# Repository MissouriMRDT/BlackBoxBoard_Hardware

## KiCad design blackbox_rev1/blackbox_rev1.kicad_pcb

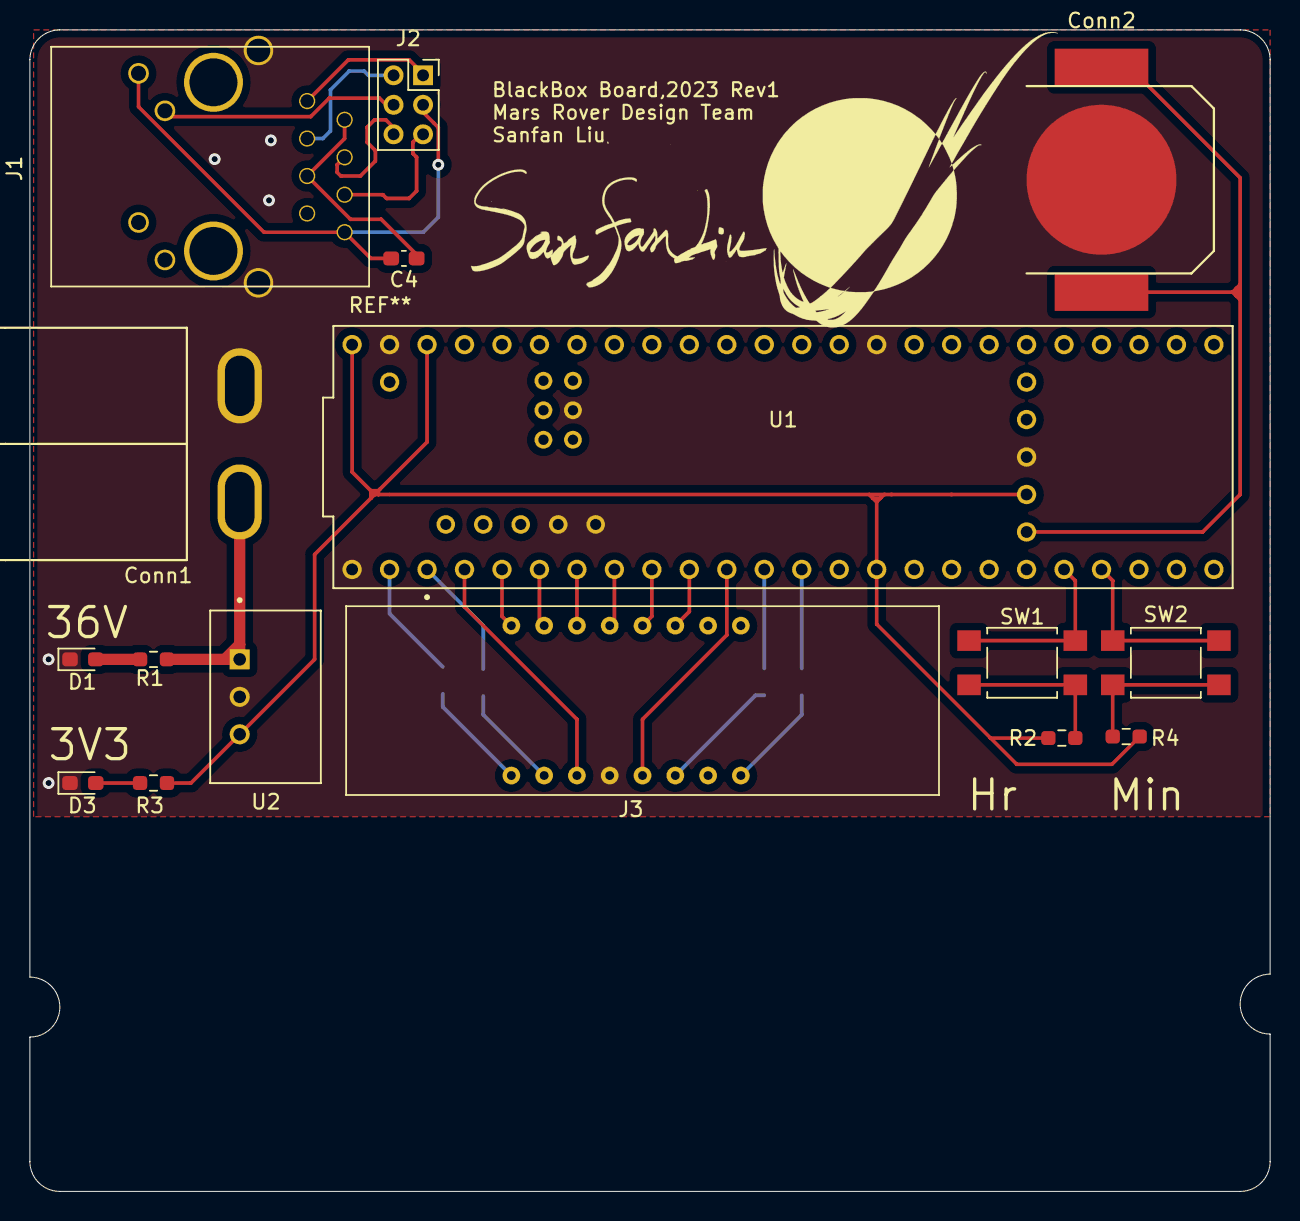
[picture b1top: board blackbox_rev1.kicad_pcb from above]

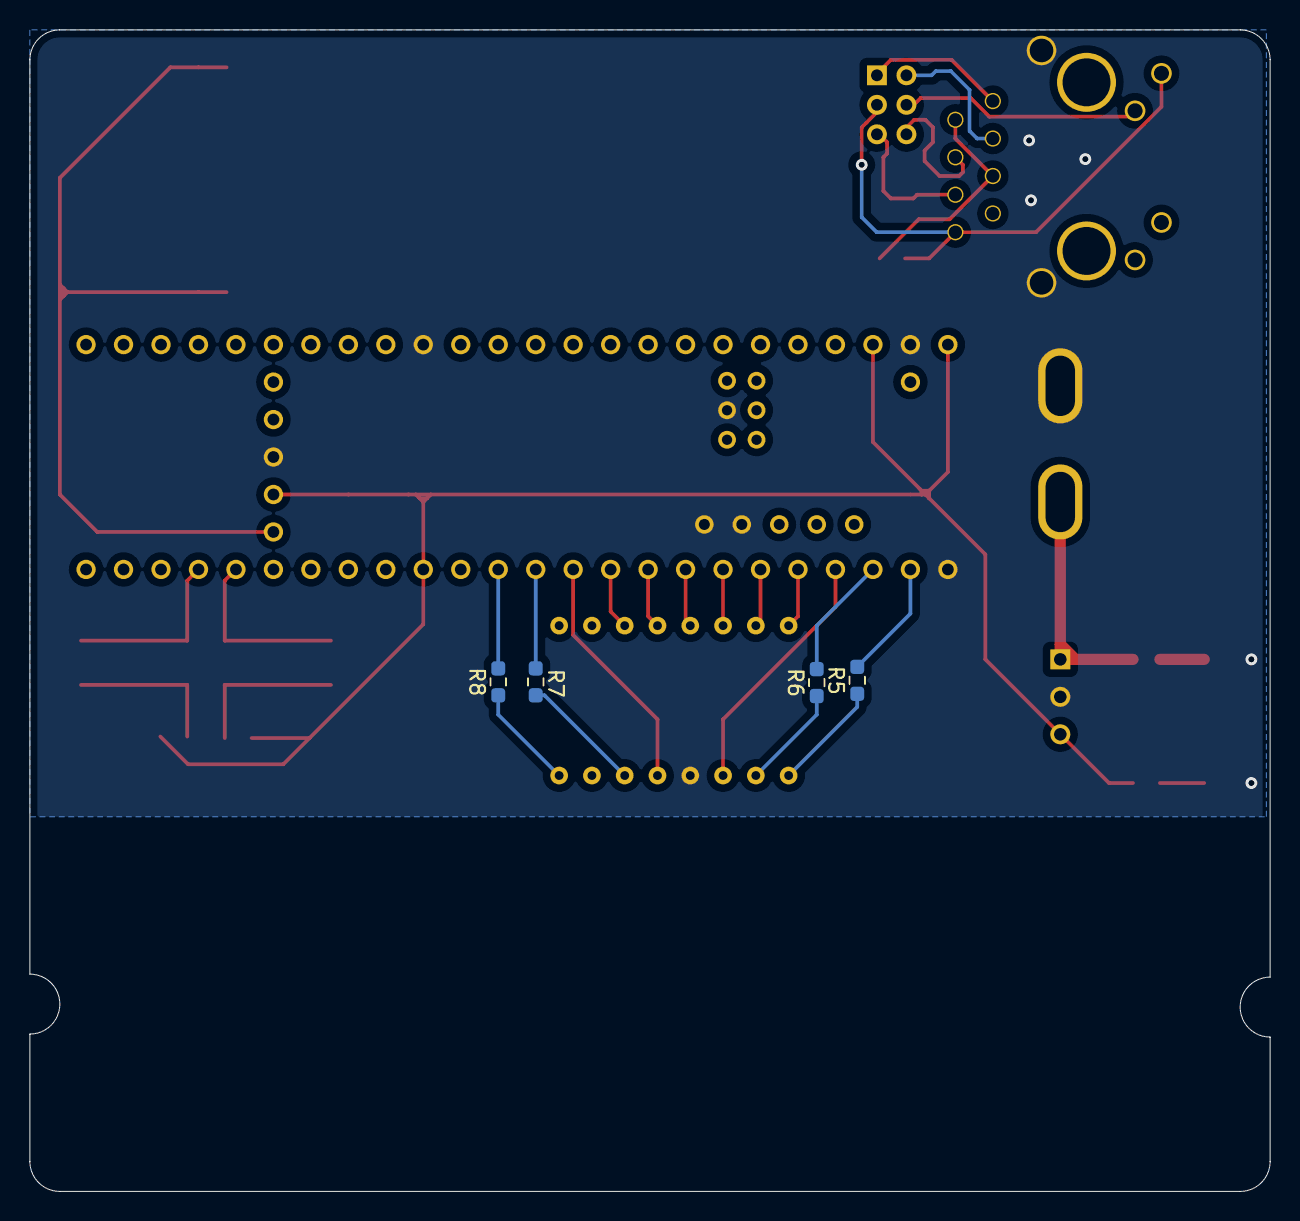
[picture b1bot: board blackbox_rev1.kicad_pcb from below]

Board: 2 copper layers, 84.1 x 78.7 mm, 20 parts (4 on the bottom side), 33 nets.

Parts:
C4: 0.1uF; C_0603_1608Metric_Pad1.08x0.95mm_HandSolder
Conn1: AndersonPP; Square_Anderson_2_H_Side_By_Side
Conn2: 12mm_Coin_Cell_Battery_Holder; CR1220_Battery_Holder
D1, D3: LED; LED_0603_1608Metric_Pad1.05x0.95mm_HandSolder
J1: RJ45_LED_Shielded; RJ45_Teensy
J2: Molex_uF_SV_06; PinSocket_2x03_P2.00mm_Vertical
J3: Conn_02x08_Counter_Clockwise; timerLED
R1: 2500; R_0603_1608Metric_Pad0.98x0.95mm_HandSolder
R2, R3, R4, R5, R6, R7, R8: 200; R_0603_1608Metric_Pad0.98x0.95mm_HandSolder
SW1, SW2: SW_Push; SW_SPST_TL3305A
U1: Teensy4.1_DEV-16771; Teensy_4_1_Vertical
U2: TSR1-2433; TSR_1-2433

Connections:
+3V3: R2.2, R3.2, R4.2, U1.3.3V_1 (3.3V), U1.3.3V_2 (3.3V), U1.3.3V_3 (3.3V), U1.VIN, U2.3 (Vout)
+36V: Conn1.2 (V+Log), R1.2, U2.1 (Vin)
/RX+: J1.4, J2.6
/RX-: J1.6, J2.5
/TX+: J1.1, J2.1
/TX-: J1.3, J2.2
Clock_SquareWave: J3.12, U1.7 (RX2)
Display_A: J3.14, U1.5 (IN2)
Display_B: J3.16, U1.3 (LRCLK2)
Display_C: J3.13, U1.6 (OUT1D)
Display_D: J3.3, U1.2 (OUT2)
Display_D1_Low: R5.2, U1.0 (RX1)
Display_D2_Low: R6.2, U1.1 (TX1)
Display_D3_Low: R7.2, U1.10 (CS1)
Display_D4_Low: R8.2, U1.11 (MOSI)
Display_E: J3.5, U1.9 (OUT1C)
Display_F: J3.11, U1.8 (TX2)
Display_G: J3.15, U1.4 (BCLK2)
GND: Conn1.1 (GND), Conn2.2, D1.1 (K), D3.1 (K), J1.SH, J3.4, U1.GND1 (GND), U1.GND2 (GND), U1.GND3 (GND), U1.GND4 (GND), U1.GND5 (GND), U1.USB_GND1 (USB_GND), U1.USB_GND2 (USB_GND), U2.2 (GND)
unnamed: C4.1, J1.2, J1.5
unnamed: C4.2, J1.8, J1.9, J2.3
unnamed: Conn2.1, U1.VBAT
unnamed: D1.2 (A), R1.1
unnamed: D3.2 (A), R3.1
unnamed: J1.10, J2.4
unnamed: J3.1, R5.1
unnamed: J3.2, R6.1
unnamed: J3.6, R7.1
unnamed: J3.8, R8.1
unnamed: R2.1, SW1.1
unnamed: R4.1, SW2.1
Sw_Hour: SW1.2, U1.28 (RX7)
Sw_Min: SW2.2, U1.29 (TX7)

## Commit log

2020-09-15 Project and Folder System Created
2020-10-16 example1
    added a wire
2020-10-16 Revert "example1"
    This reverts commit 3db448abcb6f035f2d099a4b5be1ada77b3ad630.
2020-10-21 Prototype
    Began work on schematic
2020-10-23 Placed Pins to the TIVA and connected the Pins to both SD Cards
2020-11-05 Switched from Tiva to Pi
    All that's left is finding the correct pins for the SDcard1
2021-10-12 Created the board with a teensy
2021-10-12 BOM updates
2021-10-16 Updated Capacitor on the ethernet
2021-10-20 uploaded pdf
2021-11-15 Made the footprint
    Added all the parts. I did my best?
2021-11-19 Added vias
2021-11-21 Leads helped at CDR
    Rearranged board and made edge cuts
2021-11-21 Clean up
    Deleted extra board edge and filled layers
2021-11-21 Made Gerb files
2021-12-30 generated gerbs
    BBB was already ordered.
2021-12-30 mrdt logo and drill holes added. Included in the gerbs generated in bd917c9
2021-12-30 removed rescue library
2022-09-09 initial setup
2022-09-15 schematic design
2022-09-15 added LED and buttons
2022-09-18 update bom
2022-09-30 output pdf
2022-10-17 add footprint to layout
2022-10-18 Created footprint for timerLED
2022-10-19 finish layout design
2022-10-19 switch 3v3 oki to 5v
2022-10-20 hotfix
2022-10-25 change connector direction
2022-10-26 add mounting holder
2022-10-26 coincell holder symbol
2022-11-04 added resistors to protect teensy
2022-11-04 switch teensy and pushbutton to 3v3
2022-11-19 generated gerbs
